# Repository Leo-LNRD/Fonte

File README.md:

# Fonte

Fonte 0v-12v

Objetivo: Criar uma fonte que varie entre 0v-12v com uma corrente de saída de 100mA contínua.\

Vídeo de Explicação: https://youtu.be/vfgrValPdSo

Componentes usados e seus valores:

4x Diodos de 6a 1000v	         -> 4x R$ 1,10 = R$ 4,40\
Display Voltímetro		         -> R$ 20\
2x Resistor 1k 1w			         -> 2x R$ 0,22 = R$ 0,44\
Capacitor 470uF|35v		         -> R$ 1,00\
Diodo Zener 13v|1w		         -> R$ 1,00\
Transistor MPSA42 500mA|300v	 -> R$ 5,00\
Led Alto Brilho 2-2,4v | 20mA  -> R$ 0,18\
Potenciômetro 10k|0,2w         -> R$ 7,50

Total -> R$ 39,52

Obs: Todos os valores foram consultados na internet, e eles podem variar.

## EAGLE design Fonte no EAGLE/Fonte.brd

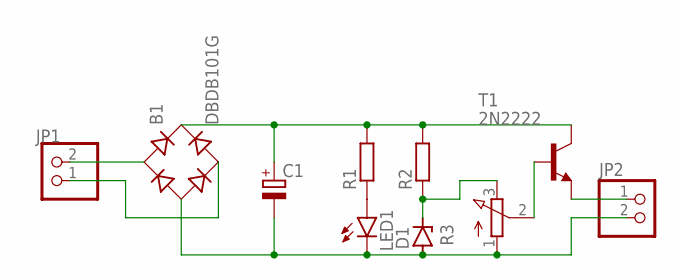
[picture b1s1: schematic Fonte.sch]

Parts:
B1: DBDB101G; DB
C1: CPOL-EUE5-10.5; E5-10,5
D1: ZENER-DIODEDO41Z10; DO41Z10
JP1, JP2: PINHD-1X2; 1X02
LED1: LED5MM
R1, R2: R-EU_0207/10; 0207/10
R3: 3RP/1610N
T1: 2N2222; TO18

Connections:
unnamed: B1.AC1, JP1.2
unnamed: LED1.A, R1.1
unnamed: B1.AC2, JP1.1
unnamed: B1.+, C1.+, R1.2, R2.2, T1.3 (C)
unnamed: B1.-, C1.-, D1.A, JP2.2, LED1.K (C), R3.1 (A)
unnamed: D1.C, R2.1, R3.3 (E)
unnamed: R3.2 (S), T1.2 (B)
unnamed: JP2.1, T1.1 (E)

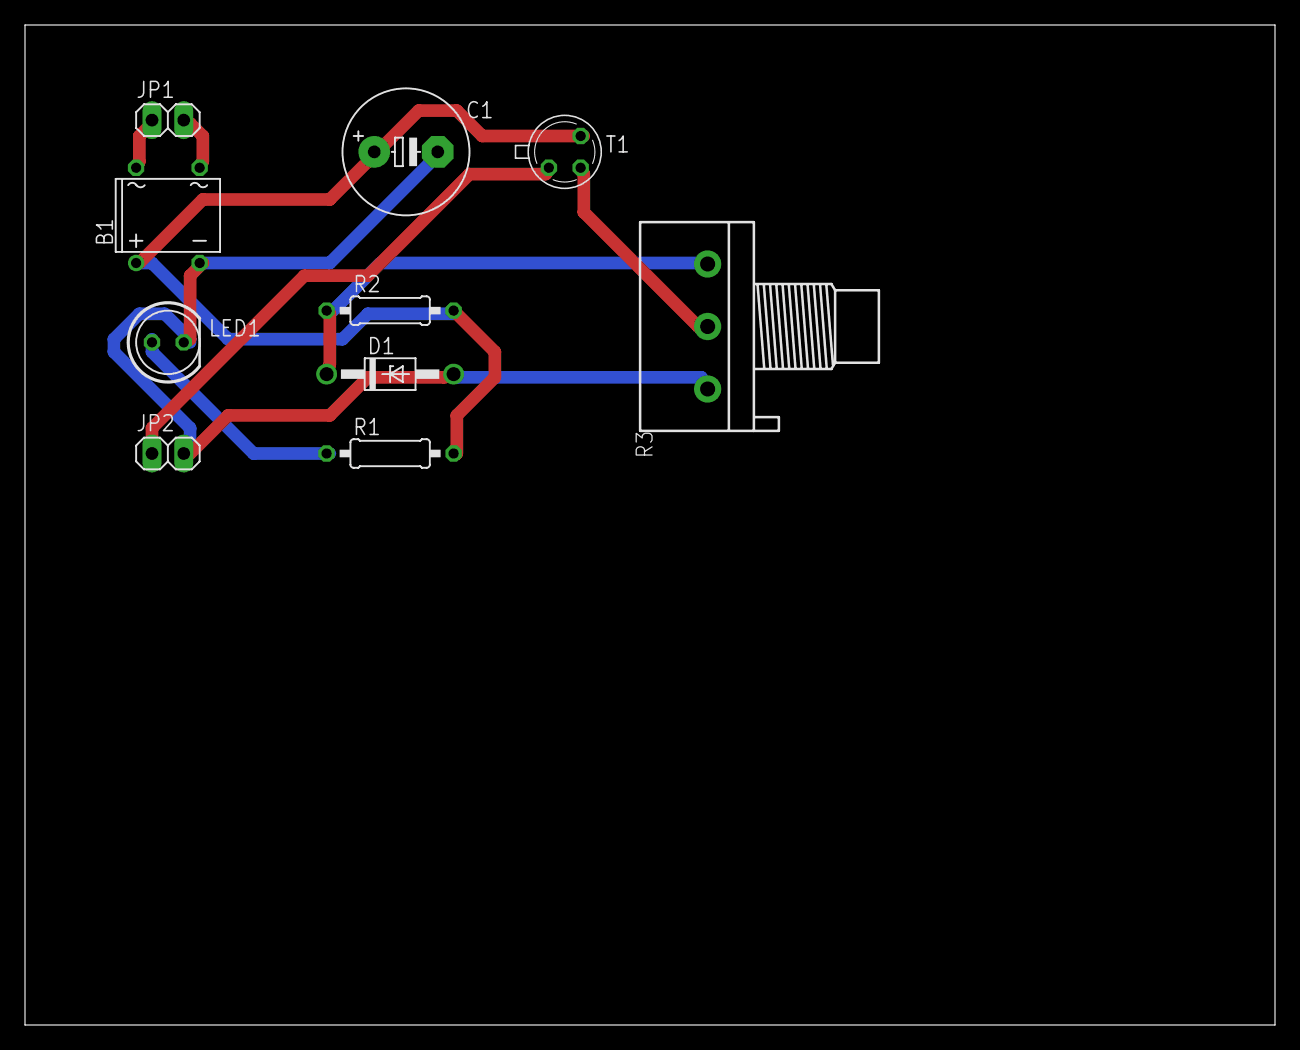
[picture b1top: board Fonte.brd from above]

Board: 2 copper layers, 100.0 x 80.0 mm, 10 parts (0 on the bottom side), 8 nets.

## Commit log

2020-06-19 Rename Circuito Falstad.txt to Fonte no Falstad.txt
